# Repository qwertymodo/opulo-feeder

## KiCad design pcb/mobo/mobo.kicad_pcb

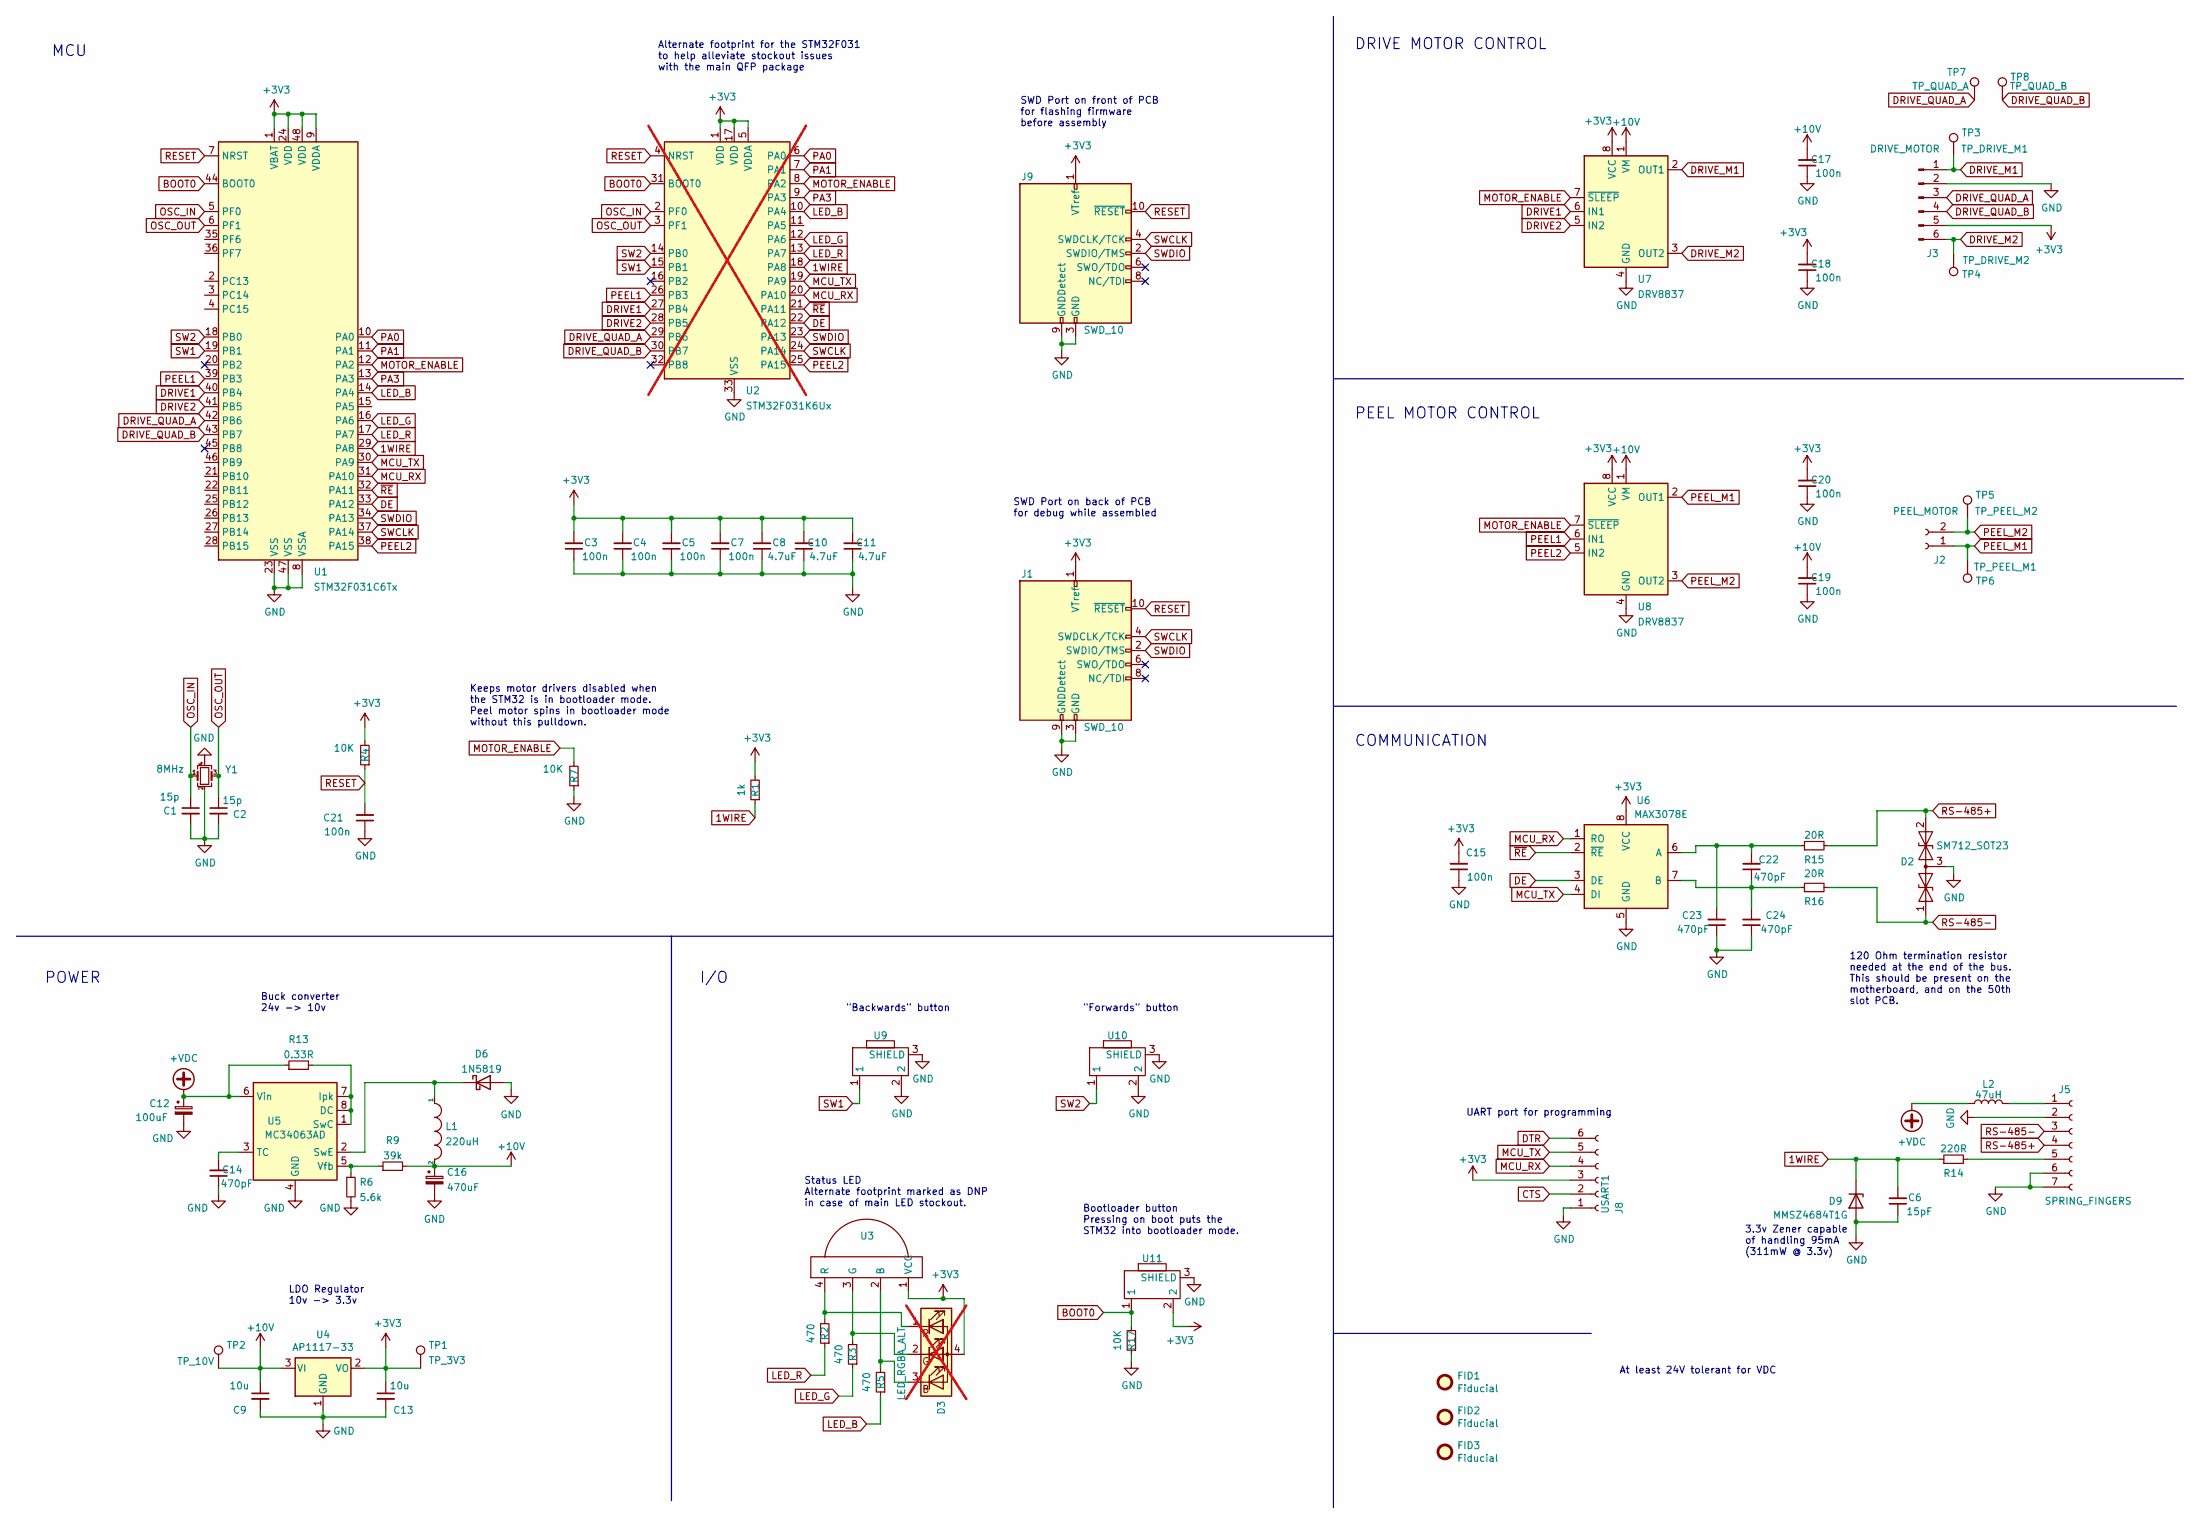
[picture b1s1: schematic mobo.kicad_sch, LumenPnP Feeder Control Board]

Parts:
C1, C2: 15p; C_0805_2012Metric; JLCPCB C1794
C3, C4, C5, C7, C15, C17, C18, C19, C20, C21: 100n; C_0805_2012Metric; JLCPCB C49678
C6: 15pF; C_0805_2012Metric; JLCPCB C49678
C8, C10, C11: 4.7uF; C_0805_2012Metric; JLCPCB C49678
C9, C13: 10u; C_0805_2012Metric; JLCPCB C15850
C12: 100uF; C_Elec_6.3x7.7
C14, C22, C23, C24: 470pF; C_0805_2012Metric; JLCPCB C49678
C16: 470uF; C_Elec_8x10.2
D2: SM712_SOT23; SOT-23; LCSC C521963
D3: LED_RGBA_ALT; LED_LiteOn_LTST-C19HE1WT; not fitted
D6: 1N5819; D_SOD-123
D9: MMSZ4684T1G; D_SOD-123; JLCPCB MMSZ4684T1G
FID1, FID2, FID3: Fiducial; Fiducial_1mm_Mask2mm
J1, J9: SWD_10; PinHeader_2x05_P1.27mm_Vertical_SMD
J2: PEEL_MOTOR; Molex_PicoBlade_53261-0271_1x02-1MP_P1.25mm_Horizontal; LCSC C2845379
J3: DRIVE_MOTOR; Molex_PicoBlade_53261-0671_1x06-1MP_P1.25mm_Horizontal; LCSC C2845383
J5: SPRING_FINGERS; AVX-9155-005-541
J8: USART1; UART_FRICTION_FIT
L1: 220uH; L_6.3x6.3_H3; LCSC C467145
L2: 47uH; L_Sunlord_SWPA5020S
R1: 1k; R_0805_2012Metric; JLCPCB C17513
R2, R3, R5: 470; R_0805_2012Metric; JLCPCB C17710
R4, R7, R17: 10K; R_0805_2012Metric; JLCPCB C17513
R6: 5.6k; R_0805_2012Metric
R9: 39k; R_0805_2012Metric
R13: 0.33R; R_0805_2012Metric
R14: 220R; R_0805_2012Metric
R15, R16: 20R; R_0805_2012Metric
TP1: TP_3V3; TestPoint_Pad_D2.0mm
TP2: TP_10V; TestPoint_Pad_D2.0mm
TP3: TP_DRIVE_M1; TestPoint_Pad_D2.0mm
TP4: TP_DRIVE_M2; TestPoint_Pad_D2.0mm
TP5: TP_PEEL_M2; TestPoint_Pad_D2.0mm
TP6: TP_PEEL_M1; TestPoint_Pad_D2.0mm
TP7: TP_QUAD_A; TestPoint_Pad_D2.0mm
TP8: TP_QUAD_B; TestPoint_Pad_D2.0mm
U1: STM32F031C6Tx; LQFP-48_7x7mm_P0.5mm
U2: STM32F031K6Ux; QFN-32-No-Paste; not fitted
U3: MHS110FRGBCT
U4: AP1117-33; SOT-223-3_TabPin2; JLCPCB C108785
U5: MC34063AD; SOIC-8_3.9x4.9mm_P1.27mm
U6: MAX3078E; SOIC-8_3.9x4.9mm_P1.27mm; JLCPCB C40031
U7, U8: DRV8837; WSON-8-1EP_2x2mm_P0.5mm_EP0.9x1.6mm
U9, U10, U11: 1TS003B-1400-3500A-CT
Y1: 8MHz; Crystal_SMD_3225-4Pin_3.2x2.5mm_HandSoldering; JLCPCB C253751

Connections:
1WIRE: C6.2, D9.1 (K), R1.1, R14.1, U1.29 (PA8), U2.18 (PA8)
+3V3: C3.2, C4.2, C5.2, C7.2, C8.2, C10.2, C11.2, C13.1, C15.2, C18.2, C20.2, D3.4 (A), J1.1 (VTref), J3.5, J8.3, J9.1 (VTref), R1.2, R4.2, TP1.1, U1.1 (VBAT), U1.9 (VDDA), U1.24 (VDD), U1.48 (VDD), U2.1 (VDD), U2.5 (VDDA), U2.17 (VDD), U3.1 (VCC), U4.2 (VO), U6.8 (VCC), U7.8 (VCC), U8.8 (VCC), U11.2
+10V: C9.1, C16.1, C17.2, C19.2, L1.2, R9.2, TP2.1, U4.3 (VI), U7.1 (VM), U8.1 (VM)
+VDC: C12.1, L2.1, R13.1, U5.6 (Vin)
BOOT0: R17.2, U1.44 (BOOT0), U2.31 (BOOT0), U11.1
CTS: J8.2
DE: U1.33 (PA12), U2.22 (PA12), U6.3 (DE)
DRIVE1: U1.40 (PB4), U2.27 (PB4), U7.6 (IN1)
DRIVE2: U1.41 (PB5), U2.28 (PB5), U7.5 (IN2)
DRIVE_M1: J3.1, TP3.1, U7.2 (OUT1)
DRIVE_M2: J3.6, TP4.1, U7.3 (OUT2)
DRIVE_QUAD_A: J3.3, TP7.1, U1.42 (PB6), U2.29 (PB6)
DRIVE_QUAD_B: J3.4, TP8.1, U1.43 (PB7), U2.30 (PB7)
DTR: J8.6
GND: C1.2, C2.2, C3.1, C4.1, C5.1, C6.1, C7.1, C8.1, C9.2, C10.1, C11.1, C12.2, C13.2, C14.1, C15.1, C16.2, C17.1, C18.1, C19.1, C20.1, C21.1, C23.1, C24.1, D2.3 (common), D6.2 (A), D9.2 (A), J1.3 (GND), J1.5 (GND), J1.9 (GNDDetect), J3.2, J5.2, J5.6, J5.7, J8.1, J9.3 (GND), J9.5 (GND), J9.9 (GNDDetect), R6.2, R7.1, R17.1, U1.8 (VSSA), U1.23 (VSS), U1.47 (VSS), U2.33 (VSS), U4.1 (GND), U5.4 (GND), U6.5 (GND), U7.4 (GND), U7.9 (GND), U8.4 (GND), U8.9 (GND), U9.2, U9.3 (SHIELD), U10.2, U10.3 (SHIELD), U11.3 (SHIELD), Y1.2, Y1.4
LED_B: R5.1, U1.14 (PA4), U2.10 (PA4)
LED_G: R3.1, U1.16 (PA6), U2.12 (PA6)
LED_R: R2.1, U1.17 (PA7), U2.13 (PA7)
MCU_RX: J8.4, U1.31 (PA10), U2.20 (PA10), U6.1 (RO)
MCU_TX: J8.5, U1.30 (PA9), U2.19 (PA9), U6.4 (DI)
MOTOR_ENABLE: R7.2, U1.12 (PA2), U2.8 (PA2), U7.7 (~SLEEP), U8.7 (~SLEEP)
unnamed: D3.3 (BK), R5.2, U3.2 (B)
unnamed: D3.2 (GK), R3.2, U3.3 (G)
unnamed: D3.1 (RK), R2.2, U3.4 (R)
unnamed: D6.1 (K), L1.1, U5.2 (SwE)
unnamed: J5.1, L2.2
unnamed: J5.5, R14.2
unnamed: R13.2, U5.1 (SwC), U5.7 (Ipk), U5.8 (DC)
unnamed: C14.2, U5.3 (TC)
unnamed: R6.1, R9.1, U5.5 (Vfb)
unnamed: C22.2, C23.2, R15.1, U6.6 (A)
unnamed: C22.1, C24.2, R16.1, U6.7 (B)
OSC_IN: C1.1, U1.5 (PF0), U2.2 (PF0), Y1.1
OSC_OUT: C2.1, U1.6 (PF1), U2.3 (PF1), Y1.3
PA0: U1.10 (PA0), U2.6 (PA0)
PA1: U1.11 (PA1), U2.7 (PA1)
PA3: U1.13 (PA3), U2.9 (PA3)
PEEL1: U1.39 (PB3), U2.26 (PB3), U8.6 (IN1)
PEEL2: U1.38 (PA15), U2.25 (PA15), U8.5 (IN2)
PEEL_M1: J2.1, TP6.1, U8.2 (OUT1)
PEEL_M2: J2.2, TP5.1, U8.3 (OUT2)
RESET: C21.2, J1.10 (~RESET), J9.10 (~RESET), R4.1, U1.7 (NRST), U2.4 (NRST)
RS-485+: D2.2 (A2), J5.4, R15.2
RS-485-: D2.1 (A1), J5.3, R16.2
SW1: U1.19 (PB1), U2.15 (PB1), U9.1
SW2: U1.18 (PB0), U2.14 (PB0), U10.1
SWCLK: J1.4 (SWDCLK/TCK), J9.4 (SWDCLK/TCK), U1.37 (PA14), U2.24 (PA14)
SWDIO: J1.2 (SWDIO/TMS), J9.2 (SWDIO/TMS), U1.34 (PA13), U2.23 (PA13)
~RE: U1.32 (PA11), U2.21 (PA11), U6.2 (~RE)

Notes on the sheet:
LDO Regulator 10v -> 3.3v
I/O
PEEL MOTOR CONTROL
COMMUNICATION
DRIVE MOTOR CONTROL
Bootloader button Pressing on boot puts the STM32 into bootloader mode.
SWD Port on front of PCB for flashing firmware before assembly
POWER
Keeps motor drivers disabled when the STM32 is in bootloader mode. Peel motor spins in bootloader mode without this pulldown.
Alternate footprint for the STM32F031 to help alleviate stockout issues with the main QFP package
"Backwards" button
3.3v Zener capable of handling 95mA (311mW @ 3.3v)
At least 24V tolerant for VDC
Status LED Alternate footprint marked as DNP in case of main LED stockout.
SWD Port on back of PCB for debug while assembled
Buck converter 24v -> 10v
"Forwards" button
MCU
120 Ohm termination resistor needed at the end of the bus. This should be present on the motherboard, and on the 50th slot PCB.
UART port for programming

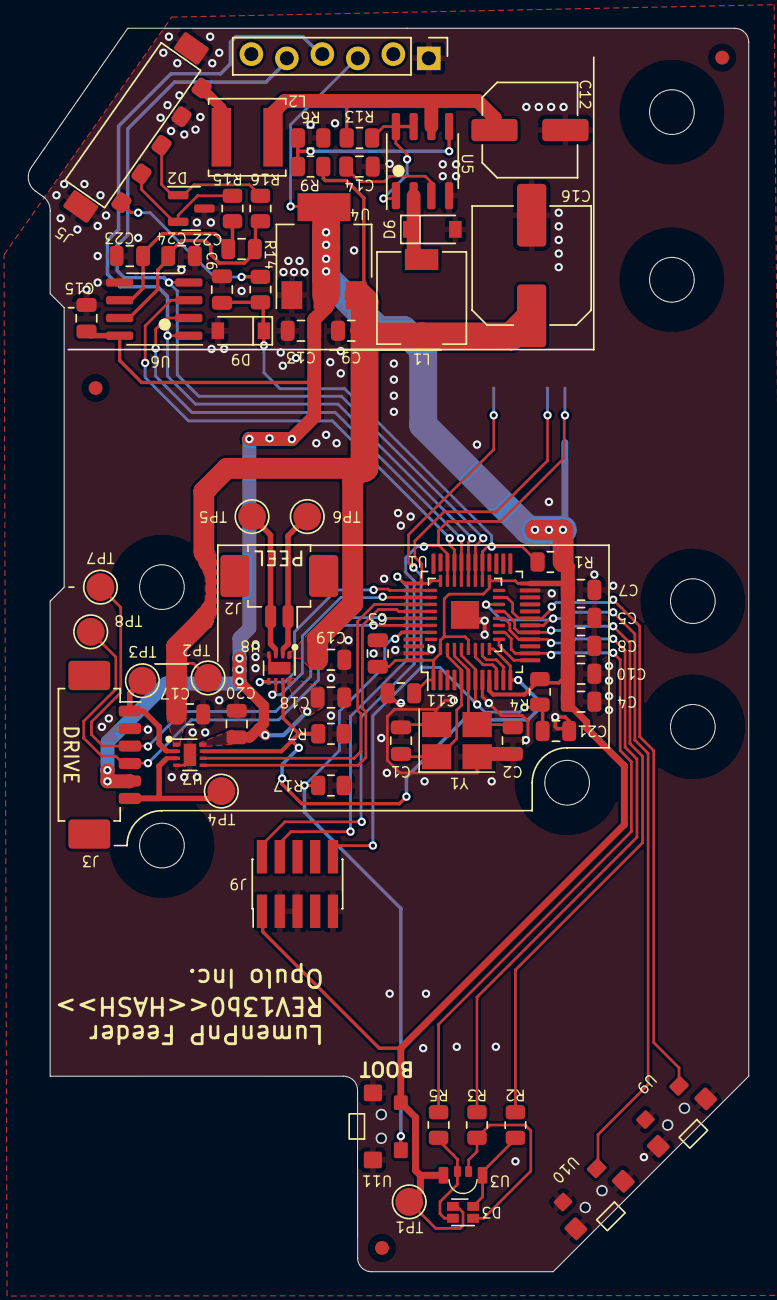
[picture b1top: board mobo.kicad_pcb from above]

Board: 2 copper layers, 51.6 x 89.0 mm, 72 parts (1 on the bottom side), 47 nets.

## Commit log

2023-08-16 changed C16 footprint and repositioned slightly
2023-09-16 updated to 8mm filter cap footprint
2023-09-16 improved keepout clearance behind countersunk hole
2023-09-16 Minor silkscreen and cosmetic fixes
2023-09-16 Update iBOM
2023-09-29 Move a few components to fit inside the power supply compartment
